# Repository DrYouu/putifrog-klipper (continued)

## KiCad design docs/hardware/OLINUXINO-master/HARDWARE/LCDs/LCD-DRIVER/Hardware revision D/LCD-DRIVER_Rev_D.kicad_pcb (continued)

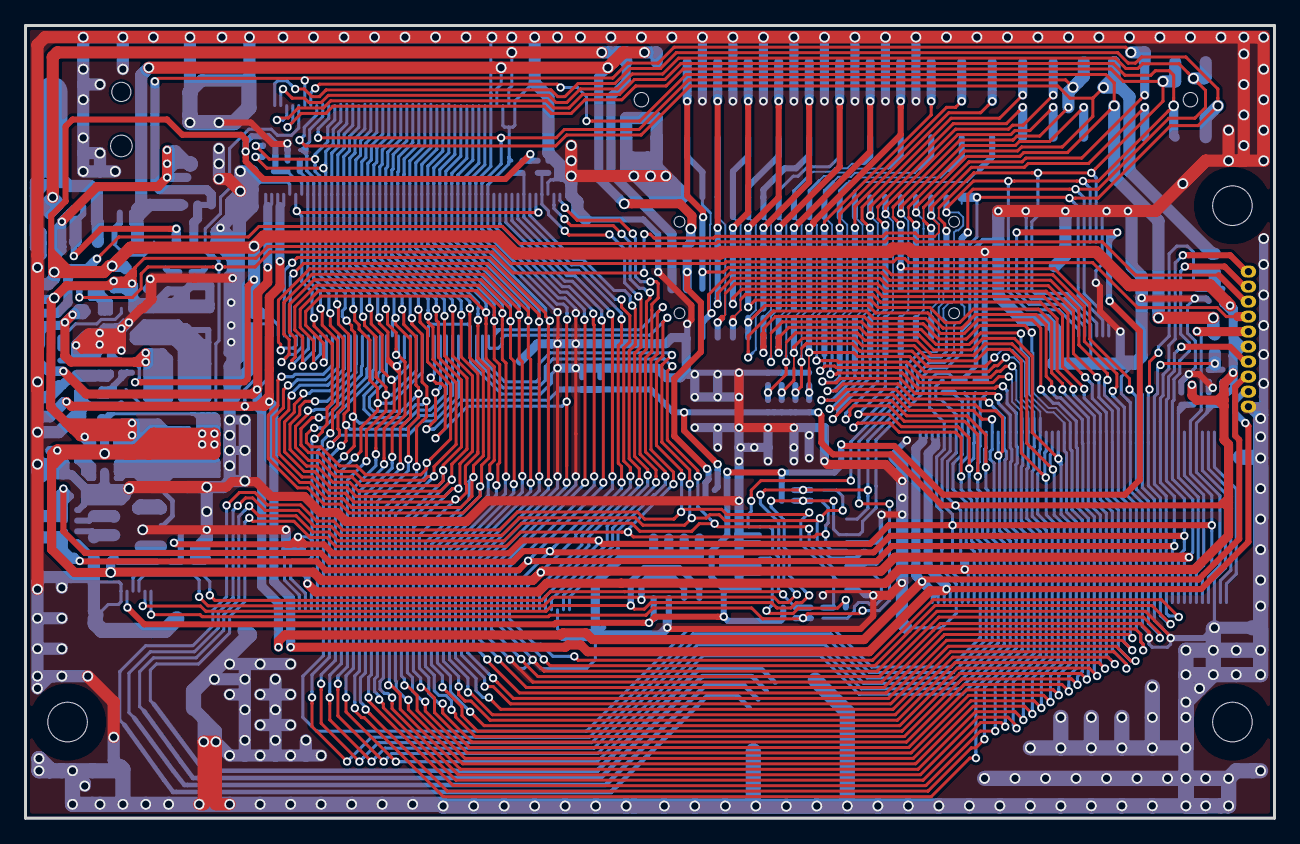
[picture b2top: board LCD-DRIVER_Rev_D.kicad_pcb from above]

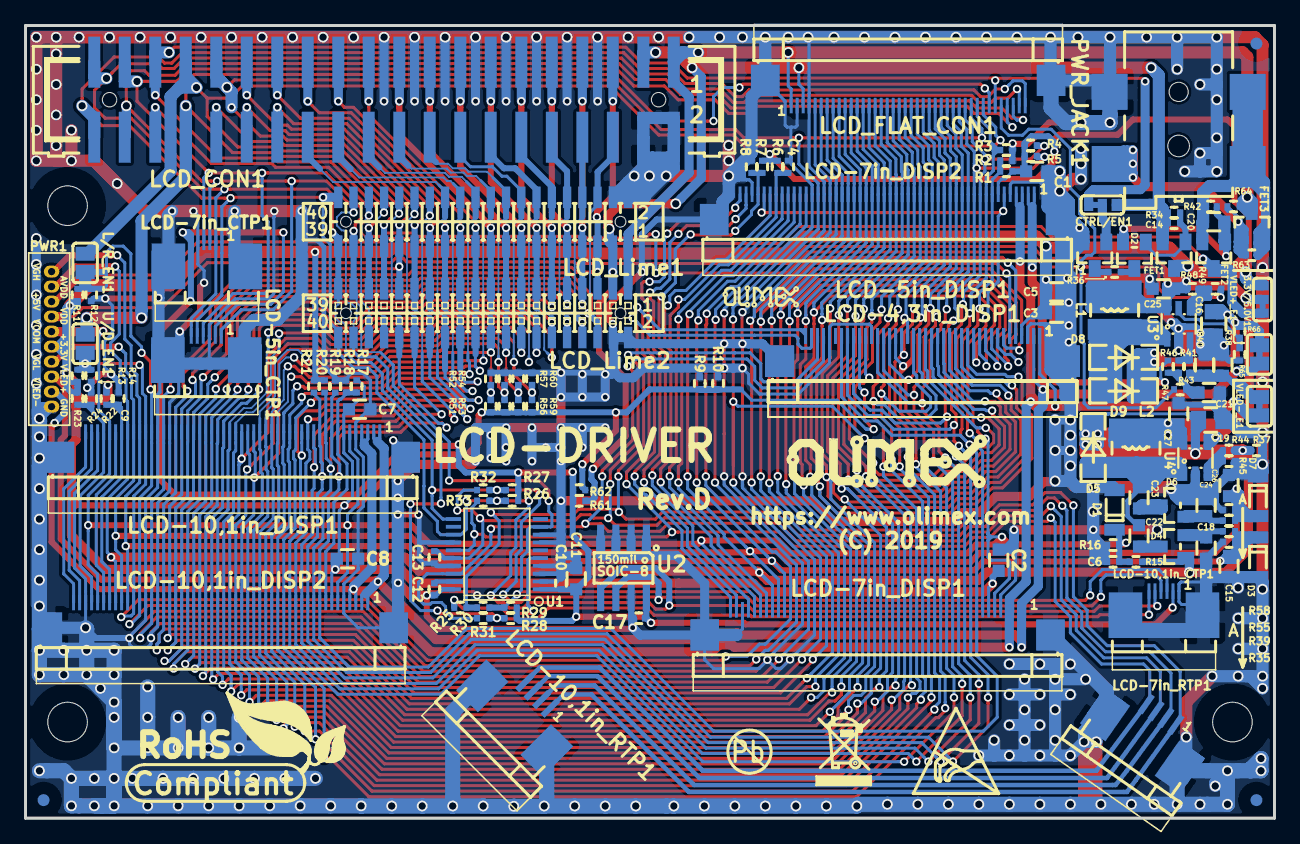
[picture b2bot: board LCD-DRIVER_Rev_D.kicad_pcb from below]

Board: 2 copper layers, 104.0 x 66.0 mm, 146 parts (143 on the bottom side), 88 nets.

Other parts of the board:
Logo-Olimex-Big: OLIMEX_LOGO_TB
Logo-Olimex_Small: LOGO_OLIMEX_80
MountingHole*: Mounting_hole_3.3mm
MountingHole*#2, MountingHole*#3: Mounting_hole_3.3mm
Sign-Antistatic: Val**; LOGO_ANTISTATIC_1
Sign-PB_Free: LOGO_PBFREE
Sign-RecycleBin: LOGO_RECYCLEBIN_1
Sign-RoHS_Compliant: Val**; LOGO_ROHS_1

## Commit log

2026-01-30 Create h
2026-01-30 Add configuration file for Leapfrog Creatr HS to Klipper
    This commit introduces a new configuration file `putifrog.cfg` for the Leapfrog Creatr HS 3D printer, adapted from the stock CreatrHS_Firmware_2.5. The configuration mirrors the stock firmware defaul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
2026-01-30 hardware-evidence: 2026-01-30 baseline + tty + buses + dt
2026-01-30 analysis: Marlin ATmega MCU communication via internal UART - port discovery needed
2026-01-30 discovery: STM32 MCU identified, communication method still unknown - not via standard serial or USB
2026-01-30 evidence: baseline A13 + MCU port investigation (STM32 identified, requires sudo)
2026-01-30 docs: executive summary - MCU port identification (requires sudo)
2026-01-30 hardware: diagnose UART/pinmux (Device Tree) with evidence - 2026-01-30
    SUMMARY:
    - Collected evidence on UART ports, kernel messages, and Device Tree configuration
    - System uses Device Tree (not legacy script.bin)
    - Only UART1 (serial@1c28400) is enabled in DTB, assigned to ttyS0 (kernel console)
    - UART0, UART2, UART3 are disabled in DTB - status='disabled'
    - Pinmux definitions exist for all UART but only UART1 is active
2026-01-31 docs
2026-01-31 docs: agregar resultados de diagnóstico UART y scripts de escaneo
